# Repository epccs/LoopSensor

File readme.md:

# Loop Sensor

From <https://github.com/epccs/LoopSensor/>

This is a collection of current loop sensor circuit boards. 

Current loop devices are normally operated over a pair of wires. They take power from the voltage and current and transmit information by controlling the current flow. I have a number of circuits that transmit two states (3mA or 10mA) depending on the output of a 555 timer. The change of state is a timing event. It is transmitted through the loop and can be remotely measured. The events can be used to tell if the 555 timing capacitance (or the current source feeding it) has changed  and how much. The current loop works over a CAT5 pair (a well-known 100 Ohm transmission line) that provides superior noise immunity. 

Note: a typical 4-20mA loop will work over phone line wire which has a higher characteristic impedance when compared with a CAT5 pair, these sensors may work over a small distance with a phone line pair, but need CAT5 for runs with more distance.

[Forums](http://rpubus.org/bb/viewforum.php?f=9)

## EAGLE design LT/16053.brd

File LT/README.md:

# Level and Temperature Sensor

Acts as a capacitive Level (e.g. fluid level) sensor.

## Overview

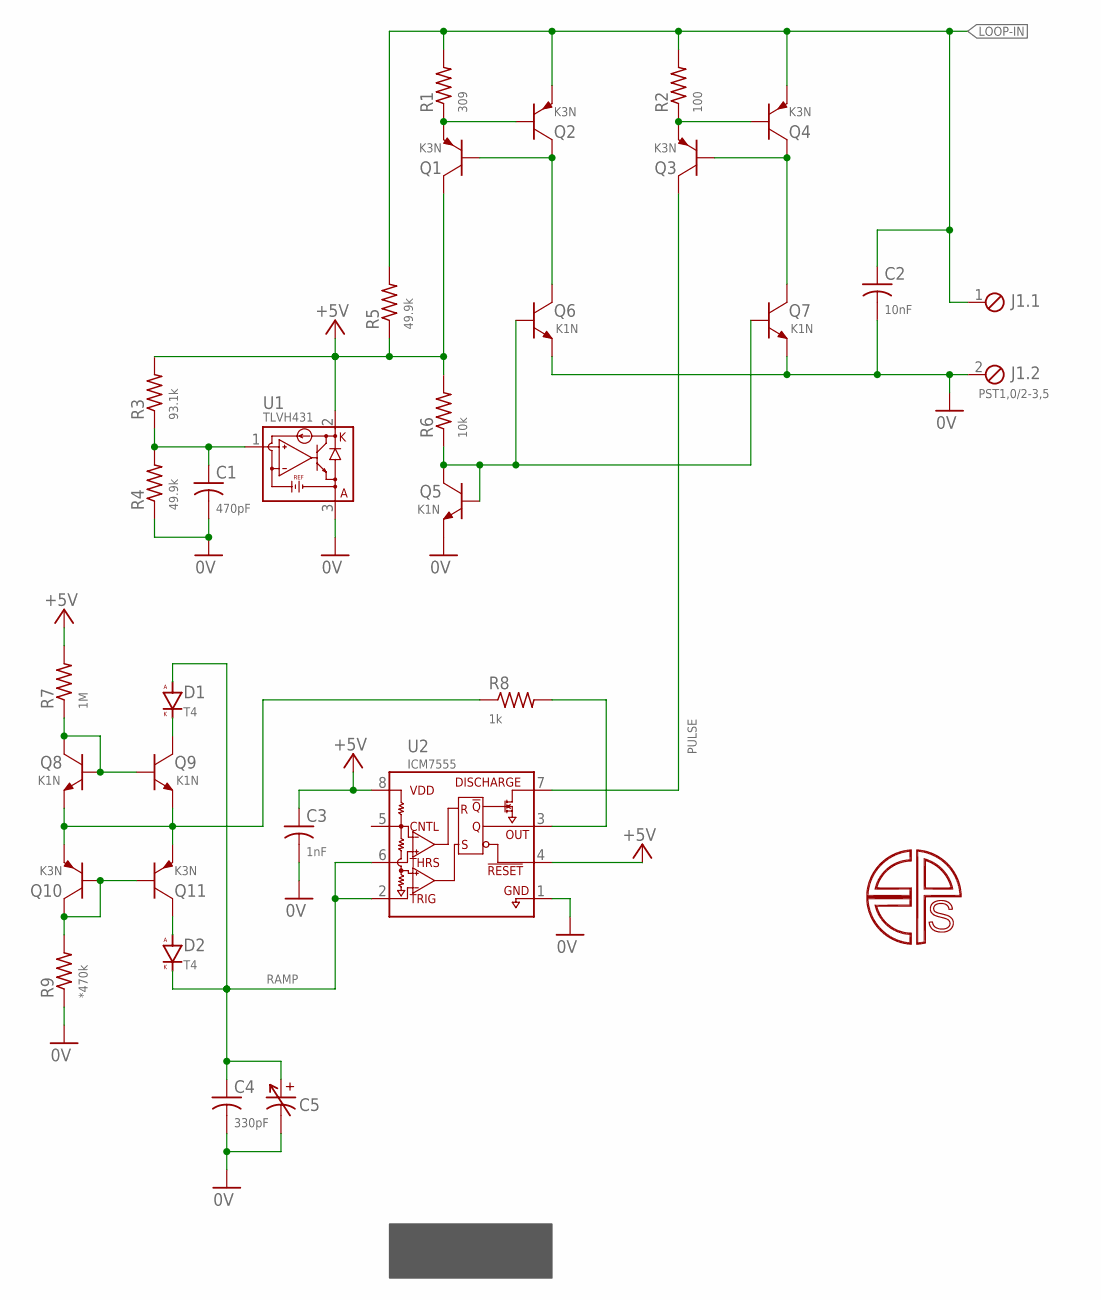
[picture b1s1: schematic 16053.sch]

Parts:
C1: 470pF; C0603(1608)
C2: 10nF; C0603(1608)
C3: 1nF; C0603(1608)
C4: 330pF; C0603(1608)
C5: HS1101
D1, D2: T4; SOD123
J1: PST1,0/2-3,5; MCV2
Q1, Q2, Q3, Q4, Q10, Q11: K3N; SOT23
Q5, Q6, Q7, Q8, Q9: K1N; SOT23
R1: 309; C0805(2012)
R2: 100; C0805(2012)
R3: 93.1k; C0805(2012)
R4, R5: 49.9k; C0805(2012)
R6: 10k; C0805(2012)
R7: 1M; C0805(2012)
R8: 1k; C0805(2012)
R9: *470k; C0805(2012)
U1: TLVH431; SOT23
U2: ICM7555; SOIC8

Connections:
0V: C1.2, C2.2, C3.2, C4.2, C5.2, J1.2, Q5.E, Q6.E, Q7.E, R4.1, R9.1, U1.3 (A), U2.1 (GND)
+5V: C3.1, Q1.C, R3.2, R5.1, R6.2, R7.2, U1.2 (K), U2.4 (!RESET), U2.8 (VDD)
LOOP-IN: C2.1, J1.1, Q2.E, Q4.E, R1.2, R2.2, R5.2
unnamed: Q10.B, Q10.C, Q11.B, R9.2
unnamed: R8.2, U2.3 (OUT)
unnamed: Q1.E, Q2.B, R1.1
unnamed: D2.A, Q11.C
unnamed: Q8.E, Q9.E, Q10.E, Q11.E, R8.1
unnamed: Q8.B, Q8.C, Q9.B, R7.1
unnamed: Q5.B, Q5.C, Q6.B, Q7.B, R6.1
unnamed: D1.C (K), Q9.C
unnamed: Q1.B, Q2.C, Q6.C
unnamed: Q3.E, Q4.B, R2.1
unnamed: Q3.B, Q4.C, Q7.C
unnamed: C1.1, R3.1, R4.2, U1.1 (REF)
PULSE: Q3.C, U2.7 (DISCHARGE)
RAMP: C4.1, C5.1, D1.A, D2.C (K), U2.2 (TRIG), U2.6 (THRS)

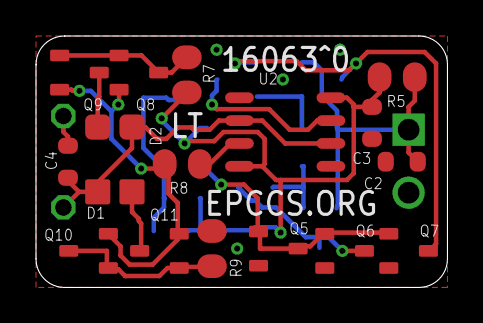
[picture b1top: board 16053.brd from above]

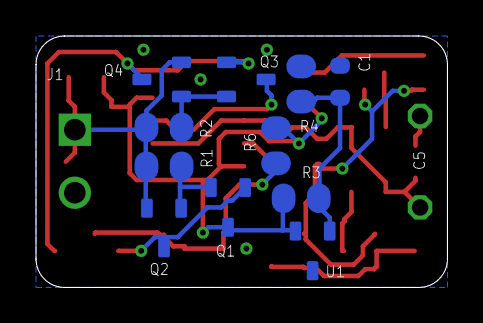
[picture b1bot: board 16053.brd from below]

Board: 2 copper layers, 22.9 x 14.0 mm, 30 parts (13 on the bottom side), 17 nets.

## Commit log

2016-11-17 :circus_tent: Added .gitattributes
2016-11-17 init
    collection of current loop sensor circuit boards
2016-11-17 HT: add humidity sensor
2016-11-17 LT: add level sensor
2016-11-17 OneShot: add pulse extender
2016-11-17 add bom and eagel files
2019-02-16 OneShot: going to use the circuit on Gravimetric so cleanup
2019-04-12 OneShot: show evaluation image
2021-02-28 MT: notes

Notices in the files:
parts and their libraries:
U-Time: Copyright (C) 2014 Ronald Steven Sutherland
Released under the Creative Commons
Attribution Share-Alike 3.0 License
http://creativecommons.org/licenses/by-sa/3.0
C-C: Copyright (C) 2013 Ronald Steven Sutherland
U-Linear: Copyright (C) 2015 Ronald Sutherland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
